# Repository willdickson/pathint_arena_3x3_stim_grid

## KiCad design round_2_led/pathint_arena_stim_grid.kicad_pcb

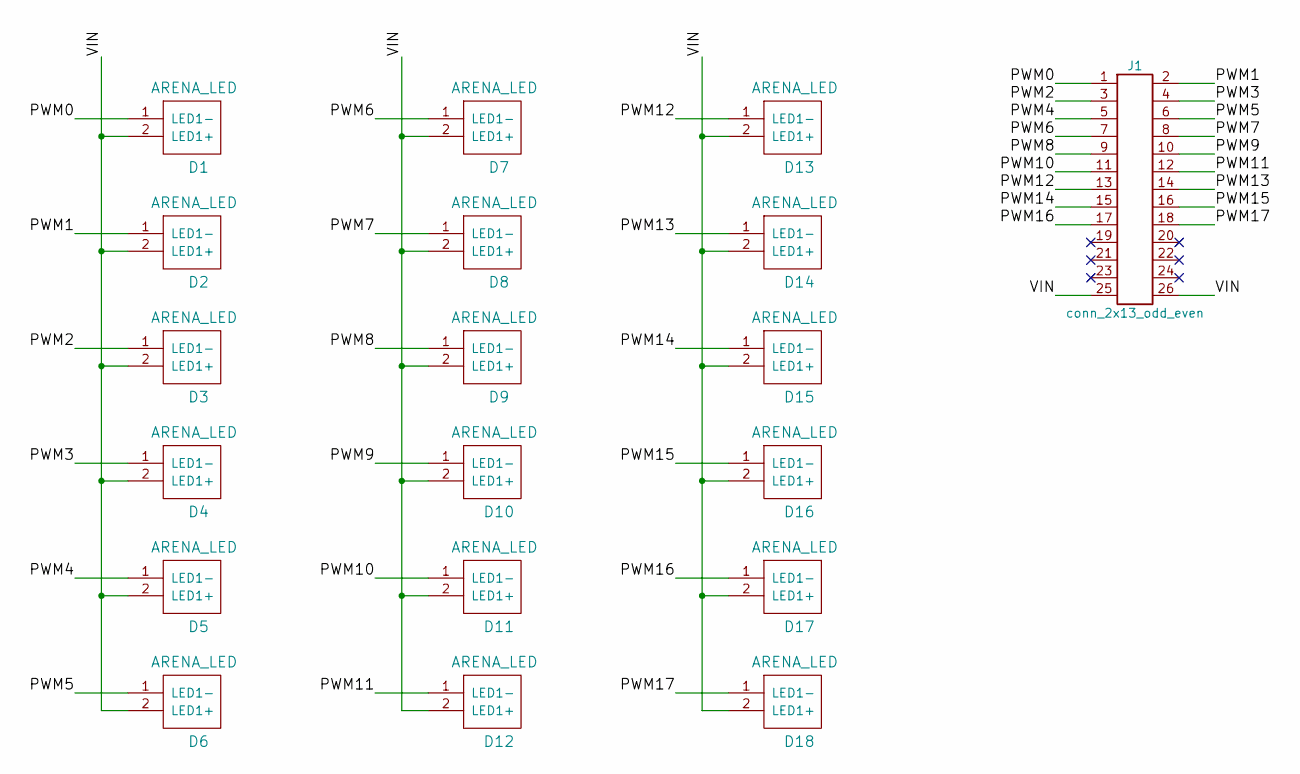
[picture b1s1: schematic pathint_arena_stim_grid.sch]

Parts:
D1, D2, D3, D4, D5, D6, D7, D8, D9, D10, D11, D12, D13, D14, D15, D16, D17, D18: ARENA_LED; SUB_ARENA
J1: conn_2x13_odd_even; 5X2_SHRD_HEADER

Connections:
/PWM0: D1.1 (LED1-), J1.1
/PWM1: D2.1 (LED1-), J1.2
/PWM2: D3.1 (LED1-), J1.3
/PWM3: D4.1 (LED1-), J1.4
/PWM4: D5.1 (LED1-), J1.5
/PWM5: D6.1 (LED1-), J1.6
/PWM6: D7.1 (LED1-), J1.7
/PWM7: D8.1 (LED1-), J1.8
/PWM8: D9.1 (LED1-), J1.9
/PWM9: D10.1 (LED1-), J1.10
/PWM10: D11.1 (LED1-), J1.11
/PWM11: D12.1 (LED1-), J1.12
/PWM12: D13.1 (LED1-), J1.13
/PWM13: D14.1 (LED1-), J1.14
/PWM14: D15.1 (LED1-), J1.15
/PWM15: D16.1 (LED1-), J1.16
/PWM16: D17.1 (LED1-), J1.17
/PWM17: D18.1 (LED1-), J1.18
/VIN: D1.2 (LED1+), D2.2 (LED1+), D3.2 (LED1+), D4.2 (LED1+), D5.2 (LED1+), D6.2 (LED1+), D7.2 (LED1+), D8.2 (LED1+), D9.2 (LED1+), D10.2 (LED1+), D11.2 (LED1+), D12.2 (LED1+), D13.2 (LED1+), D14.2 (LED1+), D15.2 (LED1+), D16.2 (LED1+), D17.2 (LED1+), D18.2 (LED1+), J1.25, J1.26

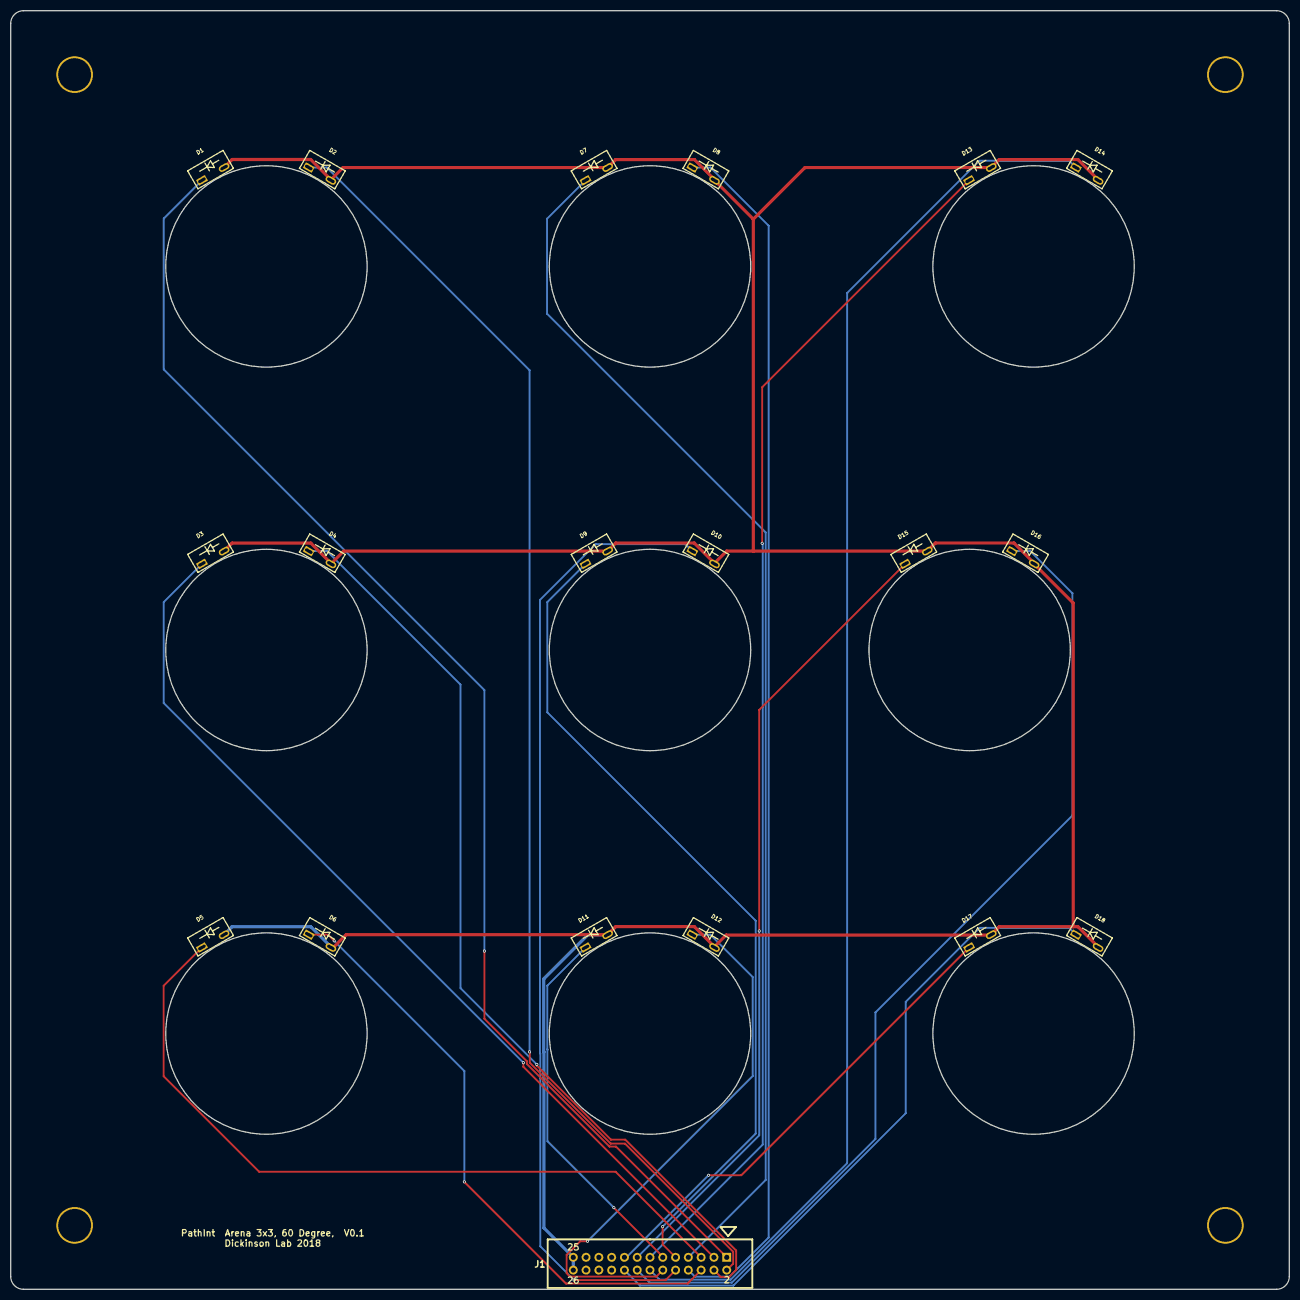
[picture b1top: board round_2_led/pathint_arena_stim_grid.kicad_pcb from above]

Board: 2 copper layers, 254.0 x 254.0 mm, 23 parts (0 on the bottom side), 19 nets.

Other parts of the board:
M1, M2, M3, M4: 0P25_THRU_HOLE

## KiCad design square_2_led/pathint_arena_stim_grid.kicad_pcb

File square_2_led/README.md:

# pathint_arena_3x3_stim_grid 
A PCB for providing light based food stimulus to a 3x3 grid of walking arenas. 

* [Schematic (PDF)](pathint_arena_stim_grid.pdf)
* [Teensy bill-of-materials](BOM.txt)

# Top View: 

# License: 
Creative Commons Attribution 4.0 International CC BY 4.0

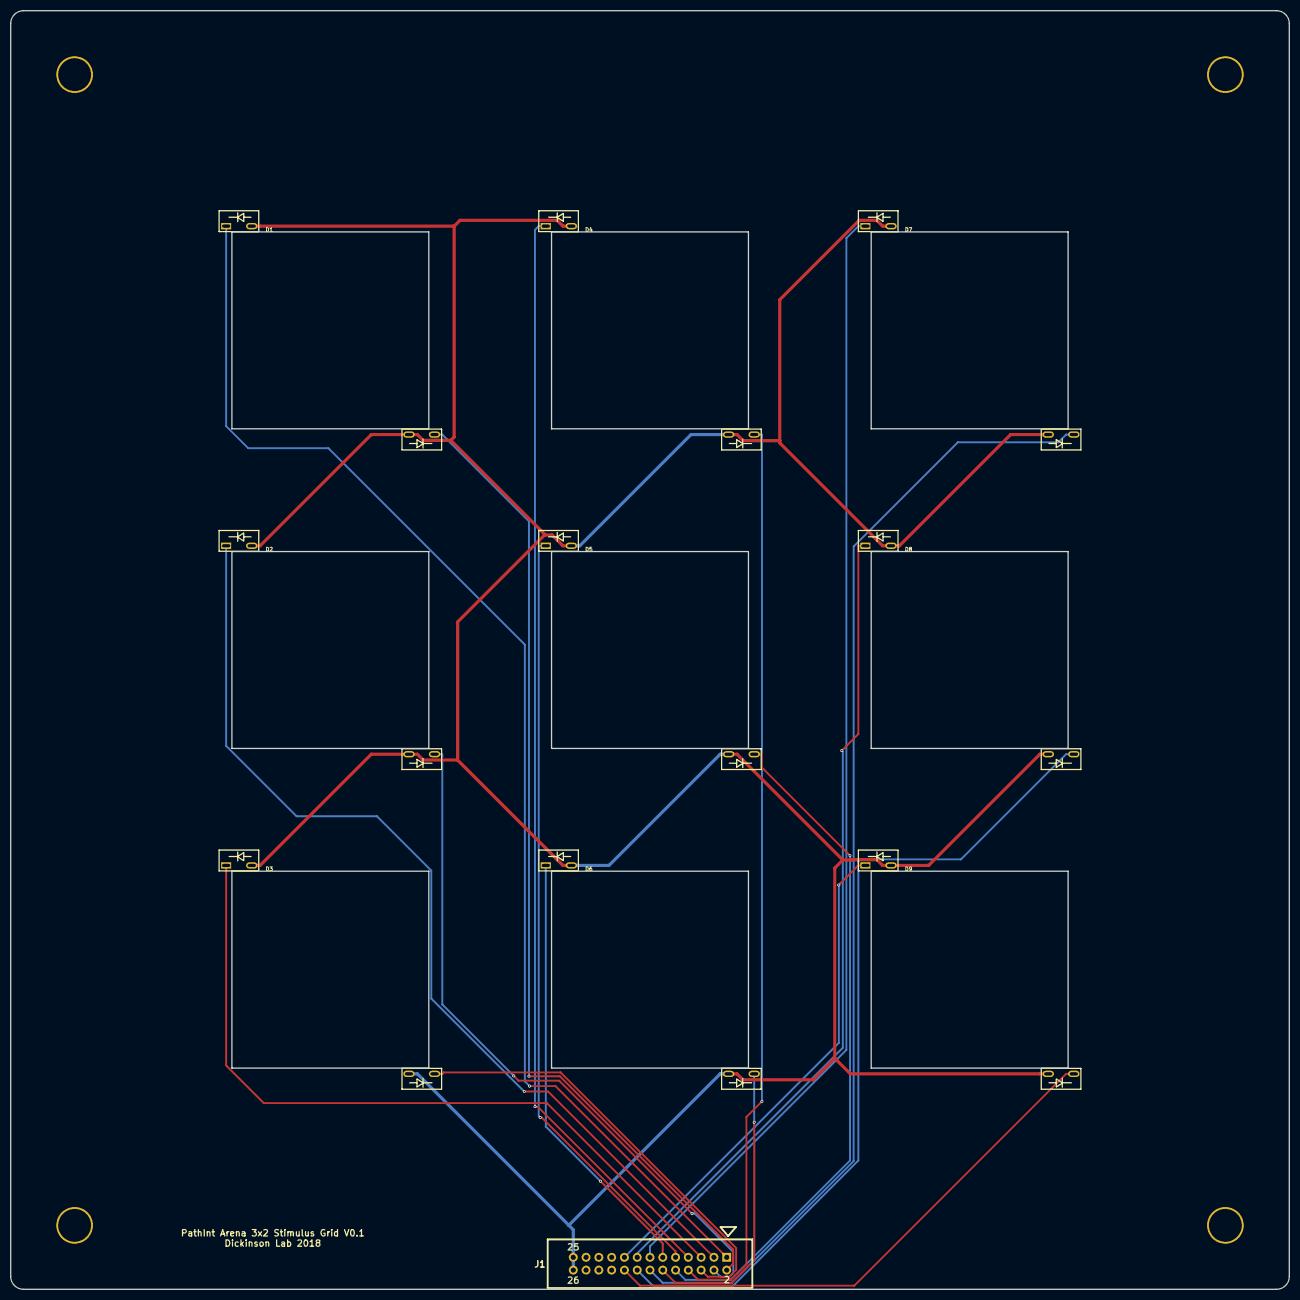
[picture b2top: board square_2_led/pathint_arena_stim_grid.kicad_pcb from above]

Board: 2 copper layers, 254.0 x 254.0 mm, 14 parts (0 on the bottom side), 19 nets.

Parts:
D1, D2, D3, D4, D5, D6, D7, D8, D9: ARENA_LED_PAIR; SUB_ARENA
J1: conn_2x13_odd_even; 5X2_SHRD_HEADER
M1, M2, M3, M4: 0P25_THRU_HOLE

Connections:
/PWM0: D1.1, J1.1
/PWM1: D1.3, J1.2
/PWM2: D2.1, J1.3
/PWM3: D2.3, J1.4
/PWM4: D3.1, J1.5
/PWM5: D3.3, J1.6
/PWM6: D4.1, J1.7
/PWM7: D4.3, J1.8
/PWM8: D5.1, J1.9
/PWM9: D5.3, J1.10
/PWM10: D6.1, J1.11
/PWM11: D6.3, J1.12
/PWM12: D7.1, J1.13
/PWM13: D7.3, J1.14
/PWM14: D8.1, J1.15
/PWM15: D8.3, J1.16
/PWM16: D9.1, J1.17
/PWM17: D9.3, J1.18
/VIN: D1.2, D1.4, D2.2, D2.4, D3.2, D3.4, D4.2, D4.4, D5.2, D5.4, D6.2, D6.4, D7.2, D7.4, D8.2, D8.4, D9.2, D9.4, J1.25, J1.26

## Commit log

2018-11-29 Project creation.
2019-09-20 Re-organized, split into square and round arenas.
2019-09-23 Added new design w/ circular arenas and leds at 60 degree angle.
